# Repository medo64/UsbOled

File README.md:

## USB OLED ##

USB OLED allows a USB CDC serial connection to SSD1306 OLED Display Modules.

### Protocol ###

This driver will present itself to the system as CDC USB device. Communication
protocol is text-based and available [here](https://github.com/medo64/UsbOled.Firmware).

---

*You can check my blog and other projects at [www.medo64.com](https://www.medo64.com/electronics/).*

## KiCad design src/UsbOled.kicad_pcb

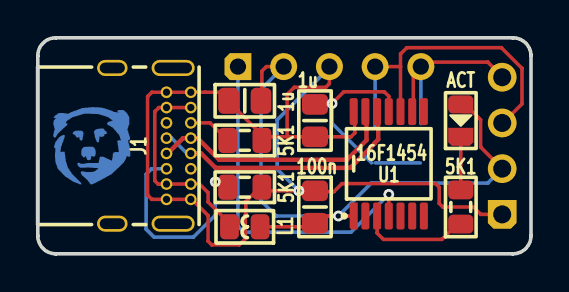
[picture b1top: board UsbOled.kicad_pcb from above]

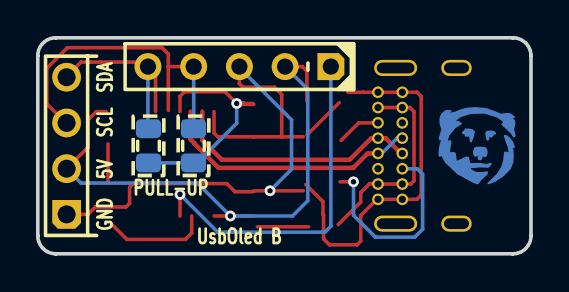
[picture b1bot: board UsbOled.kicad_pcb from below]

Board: 2 copper layers, 27.4 x 12.0 mm, 15 parts (5 on the bottom side), 13 nets.

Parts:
C1: 100n; C (0805)
C2, C3: 1u; C (0805)
DS1: ACT; DS (0805)
DS2: I2C OLED 128x32; DS OLED 128x32 I2C (4w)
ICON: Medo64; ICON Medo64
ICSP: Microchip PIC; ICSP PIC Pogo (5w)
J1: ‎USB4085; J USB C 2.0 Receptacle (16w)
L1: 40R; L Ferrite (0805)
R1, R2, R3: 5K1; R (0805)
R4, R5: 5K1; R Optional (0805)
U1: 16F1454; U Micro [PIC16F1454] (TSSOP-14)

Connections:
3V3: C3.2, R4.2, R5.2, U1.11
5V: C1.2, C2.2, DS1.2, DS2.2, ICSP.2, L1.1, U1.1
GND: C1.1, C2.1, C3.1, DS2.1, ICSP.3, J1.A01, J1.A12, J1.B01, J1.B12, R1.1, R2.1, U1.14
ICSP_VPP: ICSP.1, U1.4
LED_ACTIVE: DS1.1, R3.2
OLED_SCL: DS2.3, ICSP.4, R4.1, U1.10
OLED_SDA: DS2.4, ICSP.5, R5.1, U1.9
OUT_LED_ACTIVE: R3.1, U1.3
USB_CC1: J1.A05, R1.2
USB_CC2: J1.B05, R2.2
USB_DM: J1.A07, J1.B07, U1.12
USB_DP: J1.A06, J1.B06, U1.13
Vusb: J1.A04, J1.A09, J1.B04, J1.B11, L1.2

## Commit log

2020-12-12 Added female header part number
2020-12-13 Refactoring board layout
2020-12-13 Increased bulk capacitance
2020-12-13 Minor refactoring of ICSP position
2020-12-14 Added extra I2C pull up resistors
2020-12-14 Initial firmware commit - just skeleton
2020-12-16 Refactored I2C code to work more reliably
2020-12-16 Pull up resistors go to 3V3
2020-12-16 Refactoring pullups
2020-12-16 Added config data for I2C
2020-12-16 Added support for 128x64
2020-12-16 Fixed variable truncation
2020-12-16 Added contrast control
2020-12-16 Refactoring SSD1306 function names
2020-12-16 Basic text functions
2020-12-16 Rotated font to be column-oriented
2020-12-17 Improving text support
2020-12-17 Added large text support
2020-12-17 Avoiding multiplications to shorten stack
2020-12-17 Refactoring functions to shorten stack depth
2020-12-17 Switching to hybrid stack
2020-12-17 Refactoring out unused functions
2020-12-17 Sprinkling of const
2020-12-17 A bit of refactoring
2020-12-17 Fixing font
2020-12-17 Updated USB libraries to 2.18 (MLA v2018_11_26)
2020-12-17 Renamed Hardware into System
2020-12-17 Changed USB to polling
2020-12-17 Added check for TX readiness out output
2020-12-17 Removed USB ping-pong
2020-12-18 Basic text output
2020-12-18 Basic text support
2020-12-19 Added basic code to read/write settings
2020-12-19 Updated DFP pack
2020-12-19 Refactoring output writing to use macro
2020-12-19 Renaming variables
2020-12-19 Turning on compiler optimizations
2020-12-19 Implemented basic commands
2020-12-19 Refactored display function to have columns and rows start from 1
2020-12-19 Implemented move command
2020-12-19 Using \v for large text instead of \f
2020-12-19 Fixed cursor movement on clearAll
2020-12-19 Refactoring text setup
2020-12-19 Allowing multiple escape characters
2020-12-19 Damn it!
2020-12-19 Implemented custom character support
2020-12-19 Added drawing of custom large character
2020-12-20 Added basic graphing support
2020-12-20 Added large graph support and refactoring ssd1306 to lower memory usage
2020-12-20 Changed text a bit
2020-12-20 Fixed up settings management
2020-12-20 Added setting for brightness
2020-12-20 Removed graphing function - better done on computer anyhow
2020-12-20 Removed new line when text is written
2020-12-20 Changing how CRLF is handled to make it more PuTTY-friendly
2020-12-20 Refactoring input processing
2020-12-21 Refactoring settings a bit
2020-12-21 Renaming functions a bit
2020-12-21 A sprinkling of const
2020-12-21 Added speed setting
2020-12-21 Added function to clear line from current position
2020-12-21 Refactoring line processing to handle in-text escape characters
2020-12-21 Row cleanup supports double-height characters
2020-12-21 Added option to reset the device
2020-12-22 Buffer class cleanup
2020-12-22 Removing forgotten debug code
2020-12-22 Fixing bug with zero-length command
2020-12-22 Removing unused function
2020-12-22 Allowing inline tab characters
2020-12-22 Documentation update
2020-12-23 Implementing input buffer corruption detection
2020-12-23 Reducing program memory footprint slightly
2020-12-23 Fixing case fall-through for commands
2020-12-23 Refactoring to release a bit more program memory
2020-12-23 Updated to randomize serial number on compile
2021-01-03 Fixed via location
2021-01-03 Added notes about capacitors and resistors
2021-01-04 Added inverse
2021-01-04 Disable whole interrupt handler if not doing USB interrupt
2021-01-10 Drastically reduced LED persistence
2021-01-10 Removed randomized serial number
2021-01-10 Contrast is restored after reinitializing settings
2021-01-10 Refactoring speed settings
2021-01-10 Adding support for default inversion
2021-01-11 Allows for programmable serial
2021-01-11 Converted static to trace vias
2021-03-27 Refactored copper pours
2023-09-12 New revision
2023-09-13 Added optional I2C pull-up resistors
2023-09-14 Refactored I2C pullups to use 3V3 line
2023-09-15 Refactoring to minimum line count
2023-09-16 Changing LED setup
2023-09-16 Setting LED I/O as open-drain
2023-09-17 Updating tracks a bit
2023-09-17 Updating tracks
2024-08-21 Separated firmware into a separate repo
2024-08-22 Minor refactorings
